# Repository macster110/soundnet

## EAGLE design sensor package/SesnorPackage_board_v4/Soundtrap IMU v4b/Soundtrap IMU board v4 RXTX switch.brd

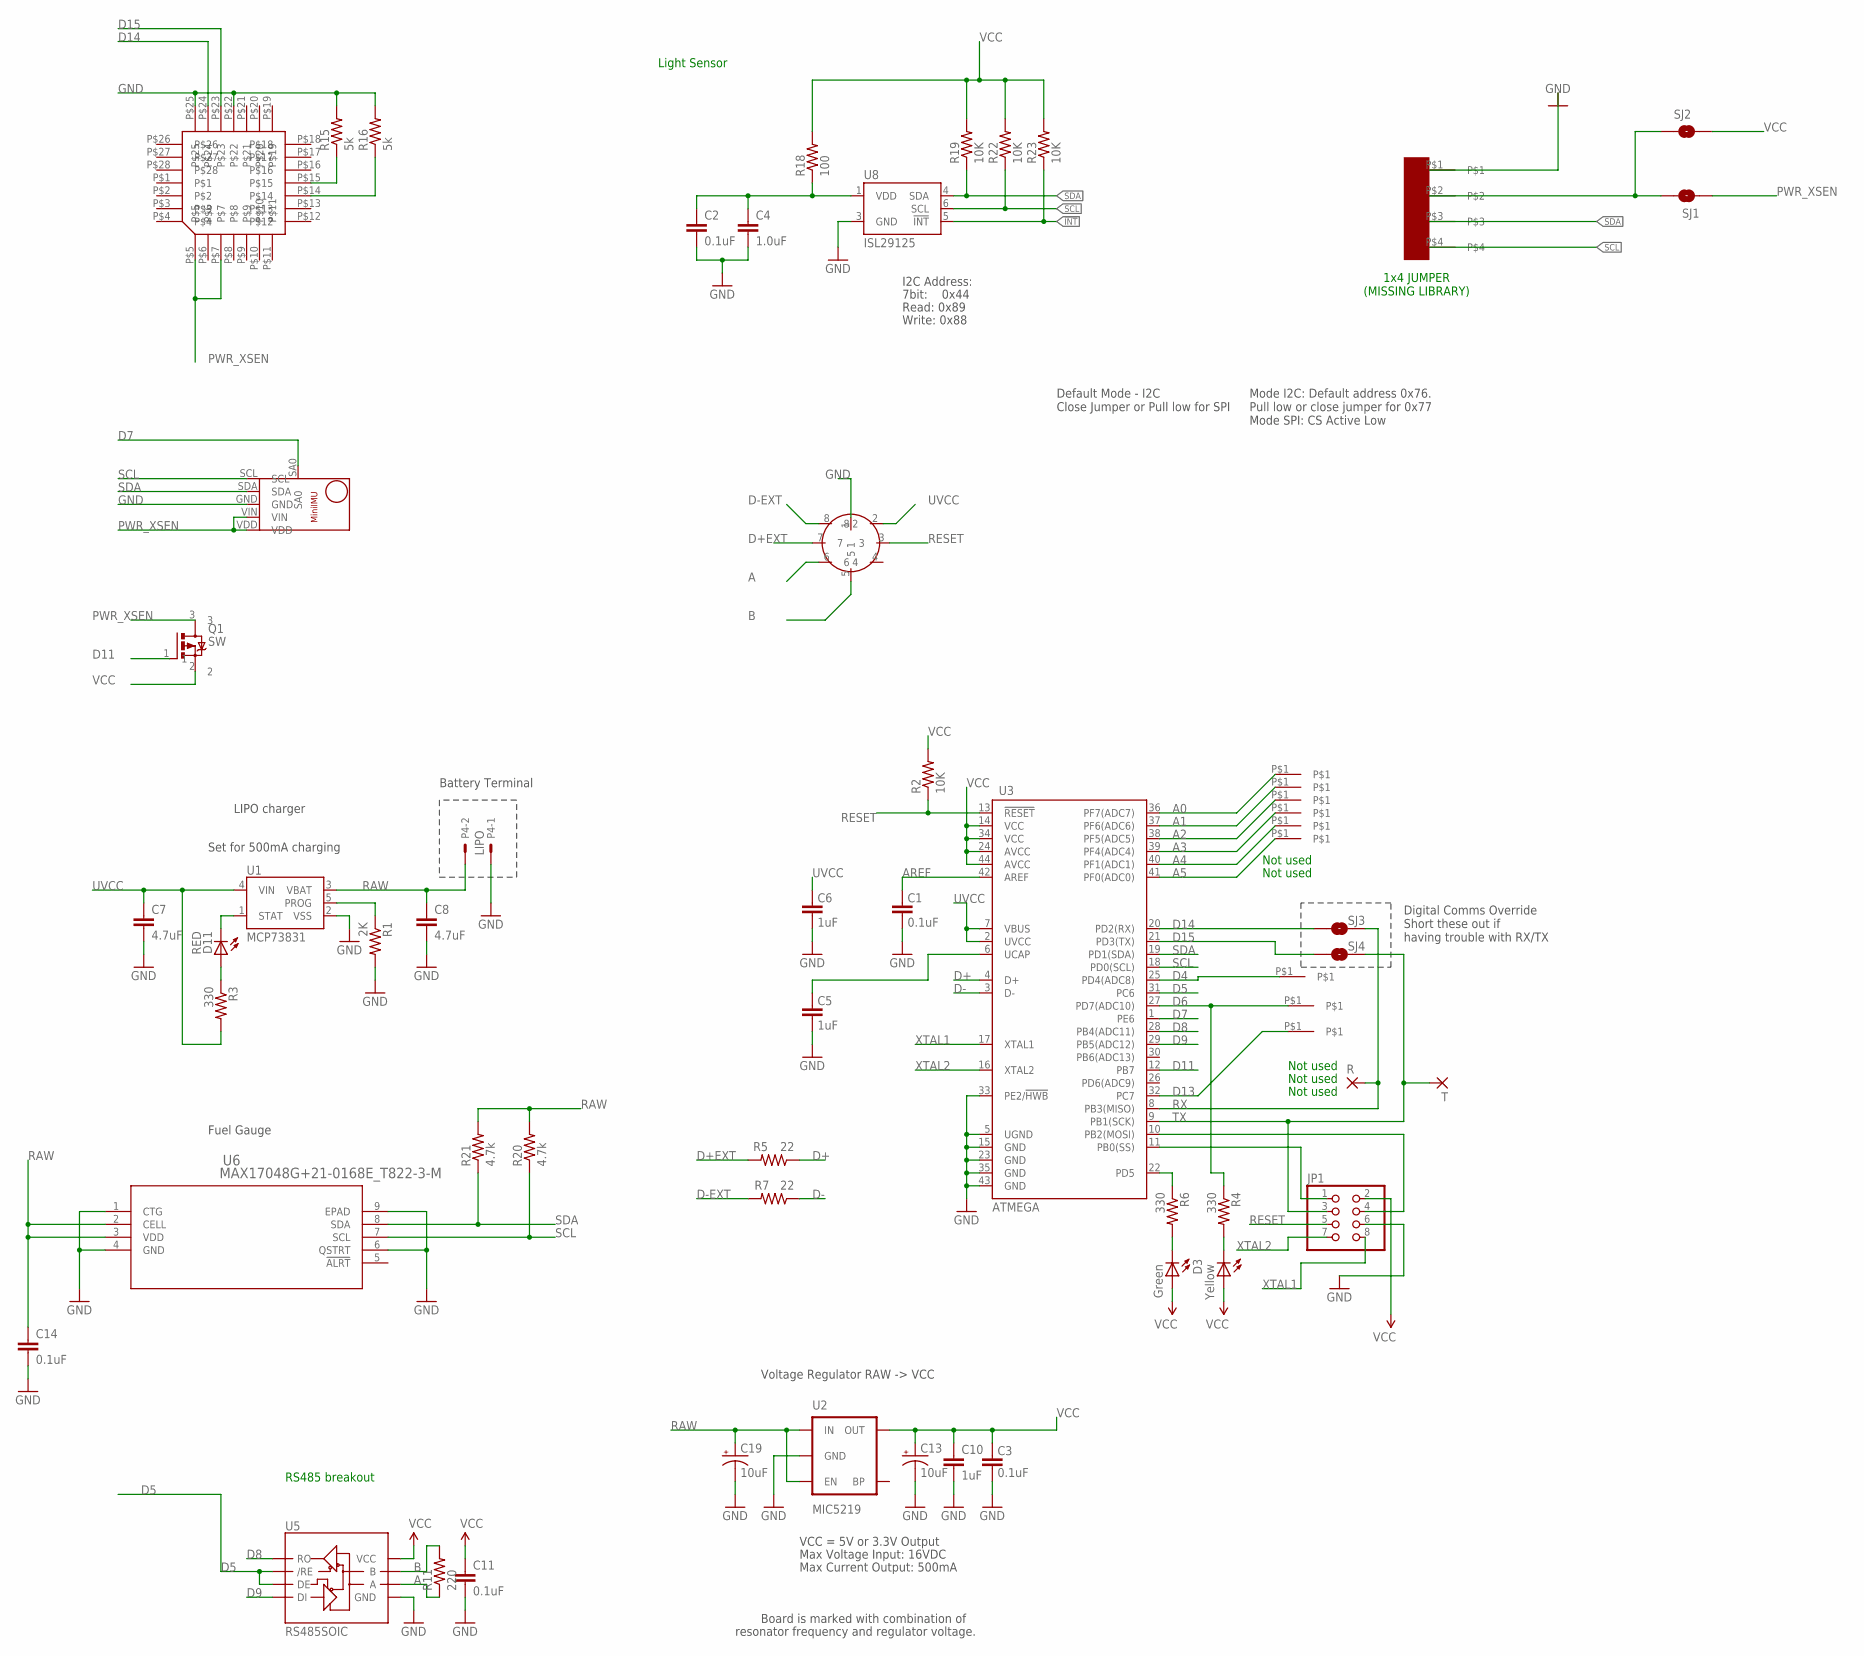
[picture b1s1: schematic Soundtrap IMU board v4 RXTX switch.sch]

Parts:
C1, C2, C3: 0.1uF; 0603-CAP
C4: 1.0uF; 0603-CAP
C5, C6, C10: 1uF; 0603-CAP
C7, C8: 4.7uF; 0402-CAP
C11, C14: 0.1uF; 0402-CAP
C13, C19: 10uF; EIA3216
D1: Yellow; LED-0603
D3: Green; LED-0603
D11: RED; LED-0603
JP1: PINHD-2X4; 2X04
P1: SUBCON_MICRO_8_EDGE_ORDERED; SUBCON_MICRO_8_EDGE
P2: MINI_IMU
P3: EXT_PRES
P4: LIPO; 22-23-2021
Q1: SW; SOT23
R: 1,6/0,9
R1: 2K; 0402-RES
R2, R19, R22, R23: 10K; 0603-RES
R3: 330; 0402-RES
R4, R6: 330; 0603-RES
R5, R7: 22; 0603-RES
R11: 220; 0402-RES
R15, R16: 5k; R0603
R18: 100; 0603-RES
R20, R21: 4.7k; 0402-RES
SJ1, SJ3, SJ4: SJ1; SJ_2S-NO
SJ2: 3v3; SJ_2S-NO
T: 1,6/0,9
U1: MCP73831; SOT23-5
U2: MIC5219; SOT23-5
U3: ATMEGA; QFN-44-NOPAD_1:1-OUTFAKES
U5: RS485SOIC; SO08
U6: MAX17048G+21-0168E_T822-3-M; 21-0168E_T822-3-M
U7: XSENSE; MC-28PLCC-SMT
U8: ISL29125; ODFN-LD-6
U$5: D4; TEST_POINT
U$6, U$7, U$8, U$9, U$10, U$11, U$12, U$13: TEST_POINT

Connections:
!INT: R23.1, U8.5 (!INT)
A: P1.6, R11.1, U5.6 (A)
A0: U3.36 (PF7(ADC7)), U$8.P$1
A1: U3.37 (PF6(ADC6)), U$9.P$1
A2: U3.38 (PF5(ADC5)), U$10.P$1
A3: U3.39 (PF4(ADC4)), U$11.P$1
A4: U3.40 (PF1(ADC1)), U$12.P$1
A5: U3.41 (PF0(ADC0)), U$13.P$1
AREF: C1.2, U3.42 (AREF)
B: P1.5, R11.2, U5.7 (B)
D4: U3.25 (PD4(ADC8)), U$5.P$1
D5: U3.31 (PC6), U5.2 (/RE), U5.3 (DE)
D6: R4.1, U3.27 (PD7(ADC10)), U$6.P$1
D7: P2.SA0, U3.1 (PE6)
D8: U3.28 (PB4(ADC11)), U5.1 (RO)
D9: U3.29 (PB5(ADC12)), U5.4 (DI)
D11: Q1.1, U3.12 (PB7)
D13: U3.32 (PC7), U$7.P$1
D14: SJ3.2, U3.20 (PD2(RX)), U7.P$24
D15: SJ4.2, U3.21 (PD3(TX)), U7.P$23
D+: R5.1, U3.4 (D+)
D+EXT: P1.7, R5.2
D-: R7.1, U3.3 (D-)
D-EXT: P1.8, R7.2
EXT_PRES_POW: P3.P$2, SJ1.2, SJ2.1
GND: C1.1, C2.2, C3.1, C4.2, C5.1, C6.1, C7.2, C8.2, C10.2, C11.2, C13.C (-), C14.2, C19.C (-), JP1.6, P1.1, P2.GND, P3.P$1, P4.1, R1.2, R15.2, R16.2, U1.2 (VSS), U2.2 (GND), U3.5 (UGND), U3.15 (GND), U3.23 (GND), U3.33 (PE2/!HWB), U3.35 (GND), U3.43 (GND), U5.5 (GND), U6.1 (CTG), U6.4 (GND), U6.6 (QSTRT), U6.9 (EPAD), U7.P$22, U7.P$25, U8.3 (GND)
MISO: JP1.1, U3.11 (PB0(SS))
MOSI: JP1.4, U3.10 (PB2(MOSI))
unnamed: C2.1, C4.1, R18.1, U8.1 (VDD)
unnamed: D11.A, R3.1
unnamed: C5.2, U3.6 (UCAP)
unnamed: D1.C, R4.2
unnamed: D3.C, R6.2
unnamed: R15.1, U7.P$15
unnamed: R16.1, U7.P$14
PROG: R1.1, U1.5 (PROG)
PWR_XSEN: P2.VDD, P2.VIN, Q1.3, SJ1.1, U7.P$5, U7.P$7
RAW: C8.1, C14.1, C19.A (+), P4.2, R20.2, R21.2, U1.3 (VBAT), U2.1 (IN), U2.3 (EN), U6.2 (CELL), U6.3 (VDD)
RESET: JP1.5, P1.3, R2.1, U3.13 (!RESET)
RX: R.1, SJ3.1, U3.8 (PB3(MISO))
SCL: P2.SCL, P3.P$4, R20.1, R22.1, U3.18 (PD0(SCL)), U6.7 (SCL), U8.6 (SCL)
SDA: P2.SDA, P3.P$3, R19.1, R21.1, U3.19 (PD1(SDA)), U6.8 (SDA), U8.4 (SDA)
STAT: D11.C, U1.1 (STAT)
TX: JP1.3, SJ4.1, T.1, U3.9 (PB1(SCK))
TXLED: R6.1, U3.22 (PD5)
UVCC: C6.2, C7.1, P1.2, R3.2, U1.4 (VIN), U3.2 (UVCC), U3.7 (VBUS)
VCC: C3.2, C10.1, C11.1, C13.A (+), D1.A, D3.A, JP1.2, Q1.2, R2.2, R18.2, R19.2, R22.2, R23.2, SJ2.2, U2.5 (OUT), U3.14 (VCC), U3.24 (AVCC), U3.34 (VCC), U3.44 (AVCC), U5.8 (VCC)
XTAL1: JP1.8, U3.17 (XTAL1)
XTAL2: JP1.7, U3.16 (XTAL2)

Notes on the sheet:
Max Voltage Input: 16VDC
Max Current Output: 500mA
Board is marked with combination of
resonator frequency and regulator voltage.
VCC = 5V or 3.3V Output
Not used
Set for 500mA charging
LIPO charger
Default Mode - I2C Close Jumper or Pull low for SPI
Mode I2C: Default address 0x76. Pull low or close jumper for 0x77 Mode SPI: CS Active Low
Light Sensor
RS485 breakout
7bit: 0x44
I2C Address:
Read: 0x89
Write: 0x88
1x4 JUMPER (MISSING LIBRARY)
Fuel Gauge
Battery Terminal
Digital Comms Override Short these out if having trouble with RX/TX
Voltage Regulator RAW -> VCC

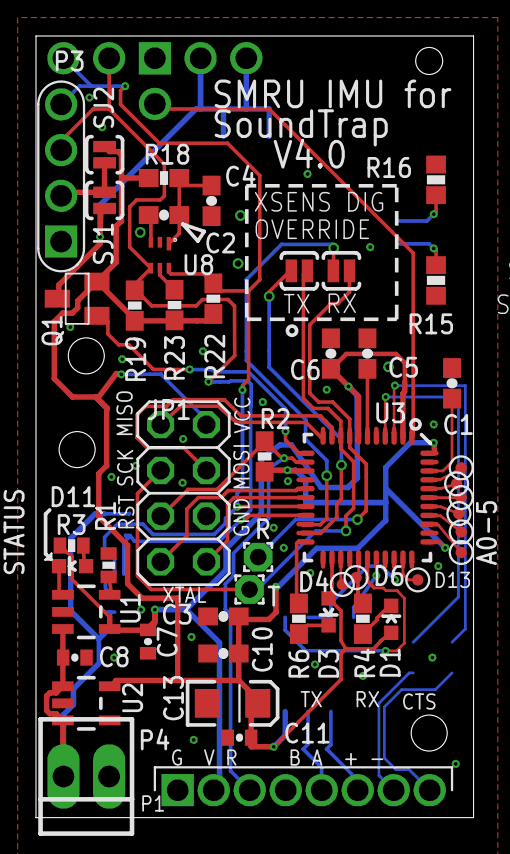
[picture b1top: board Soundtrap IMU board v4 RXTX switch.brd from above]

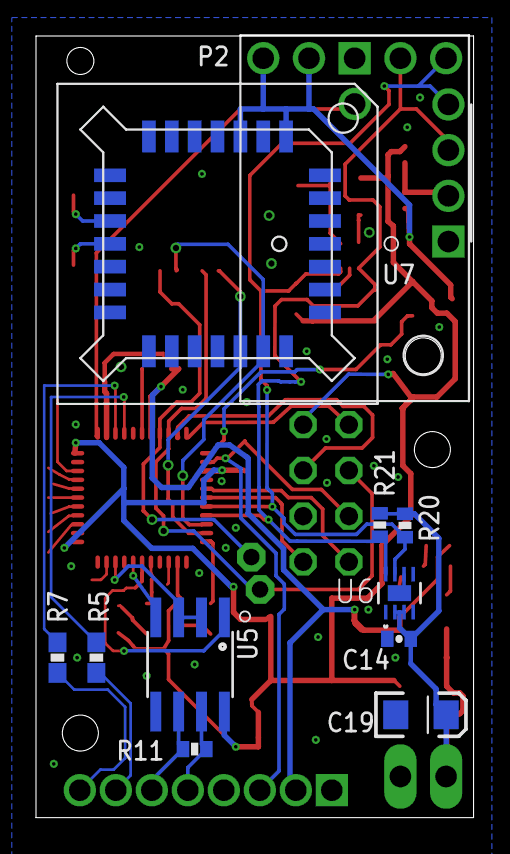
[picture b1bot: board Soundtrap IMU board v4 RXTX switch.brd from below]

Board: 2 copper layers, 24.3 x 43.4 mm, 60 parts (11 on the bottom side), 49 nets.

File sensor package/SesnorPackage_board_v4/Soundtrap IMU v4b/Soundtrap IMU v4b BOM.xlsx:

Do Not Populate | Part | Value | Device | Package | Description | OC_FARNELL
 | C1 | 0.1uF | CAP0603-CAP | 0603-CAP | Capacitor 5% tolerence
 | C2 | 0.1uF | CAP0603-CAP | 0603-CAP | Capacitor 5% tolerence
 | C3 | 0.1uF | CAP0603-CAP | 0603-CAP | Capacitor 5% tolerence
 | C4 | 1uF | CAP0603-CAP | 0603-CAP | Capacitor 5% tolerence
 | C5 | 1uF | CAP0603-CAP | 0603-CAP | Capacitor 5% tolerence
 | C6 | 1uF | CAP0603-CAP | 0603-CAP | Capacitor 5% tolerence
 | C7 | 4.7uF | CAP0402-CAP | 0402-CAP | Capacitor 5% tolerence
 | C8 | 4.7uF | CAP0402-CAP | 0402-CAP | Capacitor 5% tolerence
 | C10 | 1uF | CAP0603-CAP | 0603-CAP | Capacitor 5% tolerence
 | C11 | 0.1uF | CAP0402-CAP | 0402-CAP | Capacitor 5% tolerence
 | C13 | 10uF | CAP_POL1206 | EIA3216 | Capacitor Polarized, ESR 0.9ohm, 10V, 10% | http://uk.farnell.com/avx/tpsa106k010r0900/cap-tant-10uf-10v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
 | C14 | 0.1uF | CAP0402-CAP | 0402-CAP | Capacitor 5% tolerence
 | C19 | 10uF | CAP_POL1206 | EIA3216 | Capacitor Polarized, ESR 0.9ohm, 10V, 10% | http://uk.farnell.com/avx/tpsa106k010r0900/cap-tant-10uf-10v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
 | D1 | Yellow | LED0603 | LED-0603 | LEDs | https://www.digikey.co.uk/product-detail/en/osram-opto-semic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
 | D3 | Green | LED0603 | LED-0603 | LEDs | https://www.digikey.co.uk/product-detail/en/kingbright/APHD1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
 | D11 | RED | LED0603 | LED-0603 | LEDs | https://www.digikey.co.uk/product-detail/en/vishay-semicondu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
x | JP1 |  | PINHD-2X3 | 2X03 | 2x3 HEADER, .100" PITCH (RS Pro W82106T3825RC or similar)
x | P1 |  | SUBCON_MICRO_8_EDGE_ORDERED | SUBCON_MICRO_8_EDGE
x | P2 | MINI_IMU | MINI_IMU | MINI_IMU
x | P3 | EXT_PRES | EXT_PRES | EXT_PRES
x | P4 | LIPO | MOLEX 22-23-2021 | 22-23-2021 | .100 (2.54mm) Center Header - 2 Pin" | 1462926
 | Q1 | SW | INFINEON_BSS84P | SOT23 | p- channel -mosfet | http://uk.farnell.com/infineon/bss84ph6327xtsa2/mosfet-p-60v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
x | R |  | 1
 | R1 | 2K | RESISTOR0402-RES | 0402-RES | Resistor
 | R2 | 10K | RESISTOR0603-RES | 0603-RES | Resistor
 | R3 | 330 | RESISTOR0402-RES | 0402-RES | Resistor
 | R4 | 330 | RESISTOR0603-RES | 0603-RES | Resistor
 | R5 | 22 | RESISTOR0603-RES | 0603-RES | Resistor
 | R6 | 330 | RESISTOR0603-RES | 0603-RES | Resistor
 | R7 | 22 | RESISTOR0603-RES | 0603-RES | Resistor
x | R11 | 220 | RESISTOR0402-RES | 0402-RES | Resistor
 | R15 | 4.99k | R-US_R0603 | R0603 | RESISTOR | http://uk.farnell.com/bourns/cr0603-fx-4991elf/res-thick-fil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
 | R16 | 4.99k | R-US_R0603 | R0603 | RESISTOR | http://uk.farnell.com/bourns/cr0603-fx-4991elf/res-thick-fil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
 | R18 | 100 | RESISTOR0603-RES | 0603-RES | Resistor
 | R19 | 10k | RESISTOR0603-RES | 0603-RES | Resistor
 | R20 | 4.7k | RESISTOR0402-RES | 0402-RES | Resistor
 | R21 | 4.7k | RESISTOR0402-RES | 0402-RES | Resistor
 | R22 | 10k | RESISTOR0603-RES | 0603-RES | Resistor
 | R23 | 10k | RESISTOR0603-RES | 0603-RES | Resistor
x | SJ1 | IMU_PWR | SOLDERJUMPERNO | SJ_2S-NO | Solder Jumper
x | SJ2 | 3v3 | SOLDERJUMPERNO | SJ_2S-NO | Solder Jumper
x | SJ3 | RX | SOLDERJUMPERNO | SJ_2S-NO | Solder Jumper
x | SJ4 | TX | SOLDERJUMPERNO | SJ_2S-NO | Solder Jumper
x | T |  | 1
x | U$5 | D4 | TEST_POINT | TEST_POINT
x | U$6 | TEST_POINT | TEST_POINT | TEST_POINT
x | U$7 | TEST_POINT | TEST_POINT | TEST_POINT
x | U$8 | TEST_POINT | TEST_POINT | TEST_POINT
x | U$9 | TEST_POINT | TEST_POINT | TEST_POINT
x | U$10 | TEST_POINT | TEST_POINT | TEST_POINT
x | U$11 | TEST_POINT | TEST_POINT | TEST_POINT
x | U$12 | TEST_POINT | TEST_POINT | TEST_POINT
x | U$13 | TEST_POINT | TEST_POINT | TEST_POINT
 | U1 | MCP73831 | MCP73831 | SOT23-5 | Microchip's MCP73831 | 1332158
 | U2 | MIC5219 | V_REG_LDOSMD | SOT23-5 | Voltage Regulator LDO | 2510252
 | U3 | ATMEGA | ATMEGA32U4OUTFAKES | QFN-44-NOPAD_1:1-OUTFAKES | Atmel 44-pin 8-bit Microcontroller with 32KBytes of ISP Flash and USB Controller | 2425127
 | U6 | MAX17048G+21-0168E_T822-3-M | MAX17048G+21-0168E_T822-3-M | 21-0168E_T822-3-M | MAX17048: Battery Fuel Guage (43 is 1cell | https://www.mouser.co.uk/ProductDetail/Maxim-Integrated/MAX1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
 | U5 | RS485SOIC | RS485SOIC | SO08 |  | 2067812
 | U7 | XSENSE | XSENSE | MC-28PLCC-SMT |  | 2097220 | REPLACE WITH https://uk.farnell.com/3m/8428-21b1-rk-tp/socket-ic-plcc-28way/dp/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
 | U8 | ISL29125X | ISL29125IROZ-T7 | ODFN-6 | ISL29125 RGB Light sensor | https://www.mouser.co.uk/ProductDetail/Renesas-Intersil/ISL2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

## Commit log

2021-12-22 first read me
2021-12-22 Add particle filter code and housings
2021-12-22 Add code to simulate porpoise tracks
2021-12-22 Upload more code and pictures of the SoundNet system
2021-12-23 Create LICENSE
2021-12-23 Higher resolution figs
2021-12-23 Updated directories
2022-01-05 Diagram
2022-01-07 Sensor package code
2022-01-07 More pictures for readme's
2022-01-07 New PG screenshot
2022-01-07 New screenshot
2022-01-10 Added sensor board files
2022-01-12 Added event import function
2022-02-11 Geo reference examples
    Examples to geo-reference angles
2026-05-26 Add buzz analysis MATLAB tools and data
    Introduce a new analysis/buzzes module for buzz and call analysis: adds multiple MATLAB functions (load_event_clicks, buzz2ici, matchbuzzes, matchbuzz2track, filtbuzzesQ, filtbuzzesevent, eventbuzzes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
2026-05-26 Update README with buzz plot details
    Added a description and image for buzz plot analysis.
2026-05-26 Modify image in README for buzz analysis
    Updated image source path and dimensions in README.

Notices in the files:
parts and their libraries:
SparkFun-Aesthetics: Licensing: Creative Commons ShareAlike 4.0 International - https://creativecommons.org/licenses/by-sa/4.0
